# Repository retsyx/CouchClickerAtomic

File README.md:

# Couch Clicker Atomic

The keyboard for your couch.

Couch Clicker Atomic is a Bluetooth, mechanical key, home theater remote control designed for use with [Amity](https://github.com/retsyx/amity) - home theater control over HDMI-CEC that works! (really)

Watch the video

## Using Couch Clicker Atomic

Couch Clicker Atomic works with Amity like any other compatible remote. To read more about Amity and its operation, visit the [Amity page](https://github.com/retsyx/amity).

To clear Couch Clicker Atomic's Bluetooth pairing and to re-pair, press and hold the `Power` and `Volume Up` buttons for 6 seconds.

To reset Couch Clicker Atomic, press and hold the `Power` and `Mute` buttons for 6 seconds.

## It's a Keyboard

Couch Clicker Atomic is really just a standard wireless Bluetooth keyboard. It may work (with some customization) with other home theater devices that have bluetooth remote controls that are really keyboard devices, like Google TVs or Amazon Fire TVs.

## Hardware

### PCB

The remote is based on a Seeed Studio XIAO nRF52840 board. The PCB design and manufacturing files are [here](other/hardware).

### Keycaps

A sample design file to get your own keycaps from [Yuzu Keycaps](https://yuzukeycaps.com) is available [here](other/keycaps/yuzu.json).

### 3D Printed Case

STEP files for a 3D printed case are available [here](other/case).

### LiPo Battery

A LiPo with a JST 2 connector that fits in the case should work. The battery should be at most 10mm thick, and 30mm wide. Ensure the battery leads in the connector are the same polarity as the connector on Couch Clicker Atomic. If they are not, battery connector pins can be easily pried out with a utility knife to reverse their position in the connector.

[This LiPo battery](https://www.amazon.com/dp/B0CNLNZFQL) works well.

## Firmware

### ZMK

Download the ZMK firmware image from [here](https://github.com/retsyx/CouchClickerAtomic/releases/latest/download/cca-seeeduino_xiao_ble-zmk.uf2). Install it using the standard ZMK installation method - [documented here](https://zmk.dev/docs/user-setup#install-the-firmware).

When the remote is fully assembled in the case, to update the firmware, the remote must be reset to the bootloader. Press and hold the `Power`, `Select` and `Back` buttons for 10 seconds to reset to the bootloader.

Couch Clicker Atomic ZMK code is licensed under the [MIT license](MIT-LICENSE.md).

### KMK

Alternatively, you may prefer to use a CircuitPython based firmware with KMK. Code and instructions for installing KMK are [here](other/kmk).

Couch Clicker Atomic KMK code is licensed under the [GPLv3 license](GPLv3-LICENSE.md).

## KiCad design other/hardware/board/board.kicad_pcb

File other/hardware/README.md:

# Couch Clicker Atomic PCB

Gerber files and an example BOM file are in the [mfr folder](board/mfr/).

## BOM

* 1x [Seeed Studio XIAO BLE nRF52840](https://www.seeedstudio.com/Seeed-XIAO-BLE-nRF52840-p-5201.html)
* 15x [Cherry MX key switches, or similar, PCB mount](https://www.digikey.com/en/products/detail/cherry-americas-llc/MX1A-E1NW/20180)
* 15x [1N4148W diodes](https://www.digikey.com/en/products/detail/anbon-semiconductor-int-l-limited/1N4148W/17284377)
* 1x [JST 2.0 Connector](https://www.digikey.com/en/products/detail/jst-sales-america-inc/S2B-PH-K-S/926626)

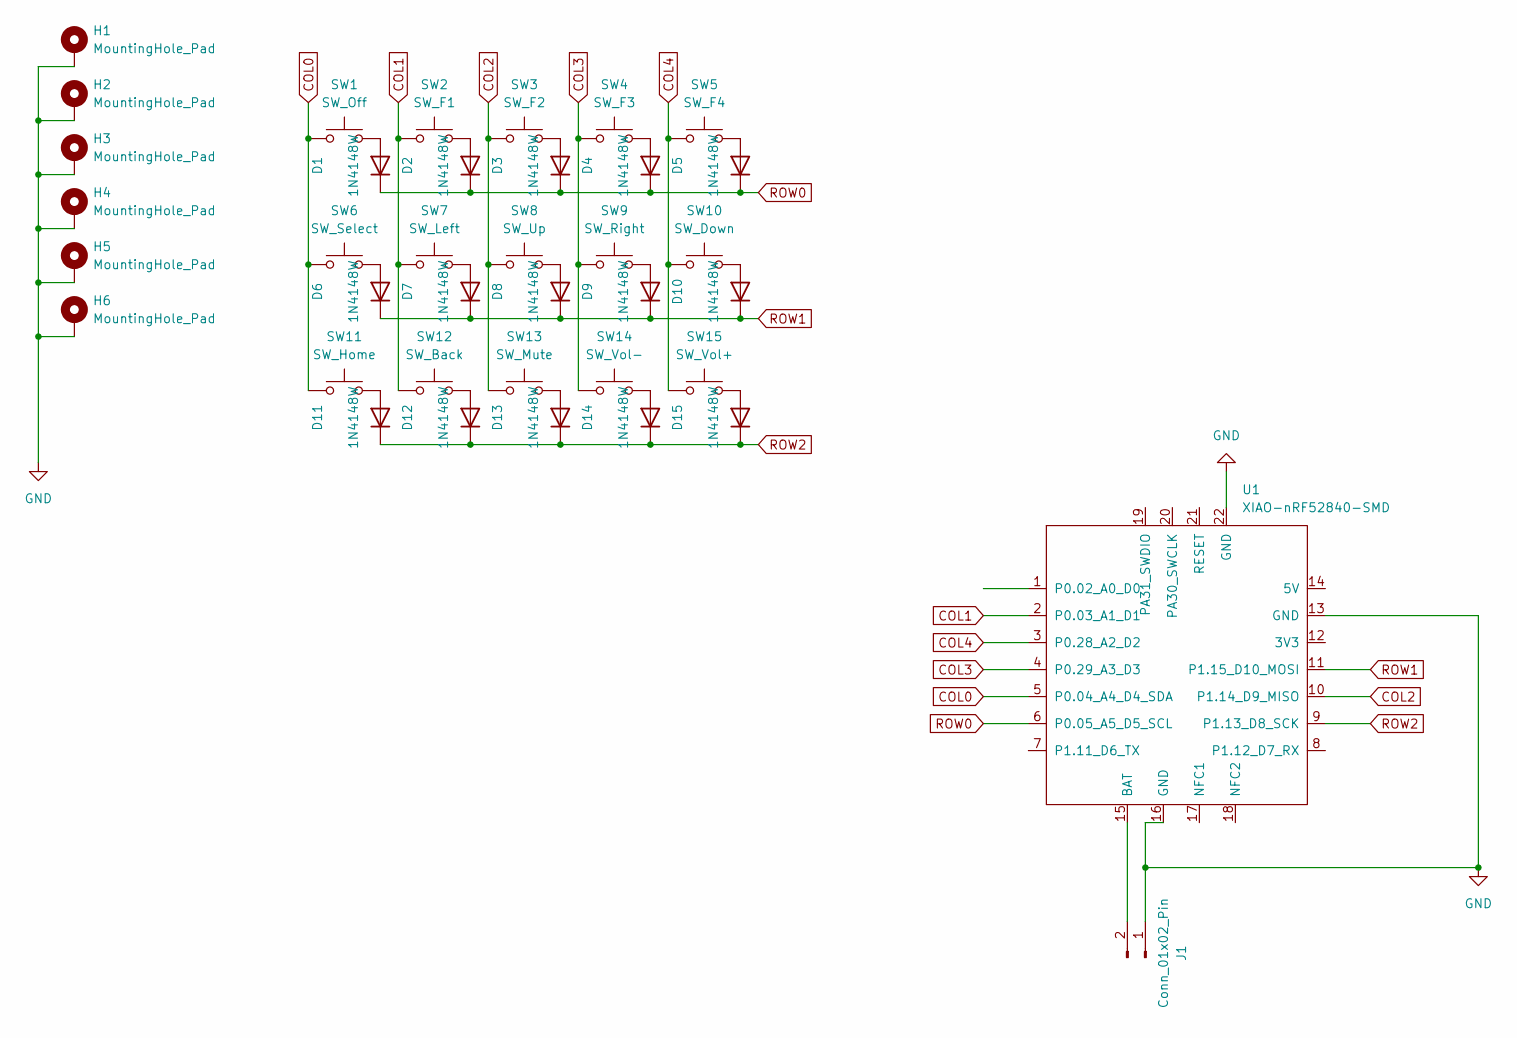
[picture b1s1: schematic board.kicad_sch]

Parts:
D1, D2, D3, D4, D5, D6, D7, D8, D9, D10, D11, D12, D13, D14, D15: 1N4148W; D_SOD-123
H1, H2, H3, H4, H5, H6: MountingHole_Pad; MountingHole_2.5mm_Pad
J1: Conn_01x02_Pin; JST_PH_S2B-PH-K_1x02_P2.00mm_Horizontal
SW1: SW_Off; SW_Cherry_MX_1.50u_PCB
SW2: SW_F1; SW_Cherry_MX_1.00u_PCB
SW3: SW_F2; SW_Cherry_MX_1.00u_PCB
SW4: SW_F3; SW_Cherry_MX_1.00u_PCB
SW5: SW_F4; SW_Cherry_MX_1.00u_PCB
SW6: SW_Select; SW_Cherry_MX_1.00u_PCB
SW7: SW_Left; SW_Cherry_MX_1.00u_PCB
SW8: SW_Up; SW_Cherry_MX_1.00u_PCB
SW9: SW_Right; SW_Cherry_MX_1.00u_PCB
SW10: SW_Down; SW_Cherry_MX_1.00u_PCB
SW11: SW_Home; SW_Cherry_MX_1.00u_PCB
SW12: SW_Back; SW_Cherry_MX_1.00u_PCB
SW13: SW_Mute; SW_Cherry_MX_1.00u_PCB
SW14: SW_Vol-; SW_Cherry_MX_1.00u_PCB
SW15: SW_Vol+; SW_Cherry_MX_1.00u_PCB
U1: XIAO-nRF52840-SMD

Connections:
COL0: SW1.1, SW6.1, SW11.1, U1.5 (P0.04_A4_D4_SDA)
COL1: SW2.1, SW7.1, SW12.1, U1.2 (P0.03_A1_D1)
COL2: SW3.1, SW8.1, SW13.1, U1.10 (P1.14_D9_MISO)
COL3: SW4.1, SW9.1, SW14.1, U1.4 (P0.29_A3_D3)
COL4: SW5.1, SW10.1, SW15.1, U1.3 (P0.28_A2_D2)
GND: H1.1, H2.1, H3.1, H4.1, H5.1, H6.1, J1.1, U1.13 (GND), U1.16 (GND), U1.22 (GND)
unnamed: D1.2 (A), SW1.2
unnamed: D2.2 (A), SW2.2
unnamed: D3.2 (A), SW3.2
unnamed: D4.2 (A), SW4.2
unnamed: D5.2 (A), SW5.2
unnamed: D6.2 (A), SW6.2
unnamed: D7.2 (A), SW7.2
unnamed: D8.2 (A), SW8.2
unnamed: D9.2 (A), SW9.2
unnamed: D10.2 (A), SW10.2
unnamed: D11.2 (A), SW11.2
unnamed: D12.2 (A), SW12.2
unnamed: D13.2 (A), SW13.2
unnamed: D14.2 (A), SW14.2
unnamed: D15.2 (A), SW15.2
unnamed: J1.2, U1.15 (BAT)
ROW0: D1.1 (K), D2.1 (K), D3.1 (K), D4.1 (K), D5.1 (K), U1.6 (P0.05_A5_D5_SCL)
ROW1: D6.1 (K), D7.1 (K), D8.1 (K), D9.1 (K), D10.1 (K), U1.11 (P1.15_D10_MOSI)
ROW2: D11.1 (K), D12.1 (K), D13.1 (K), D14.1 (K), D15.1 (K), U1.9 (P1.13_D8_SCK)

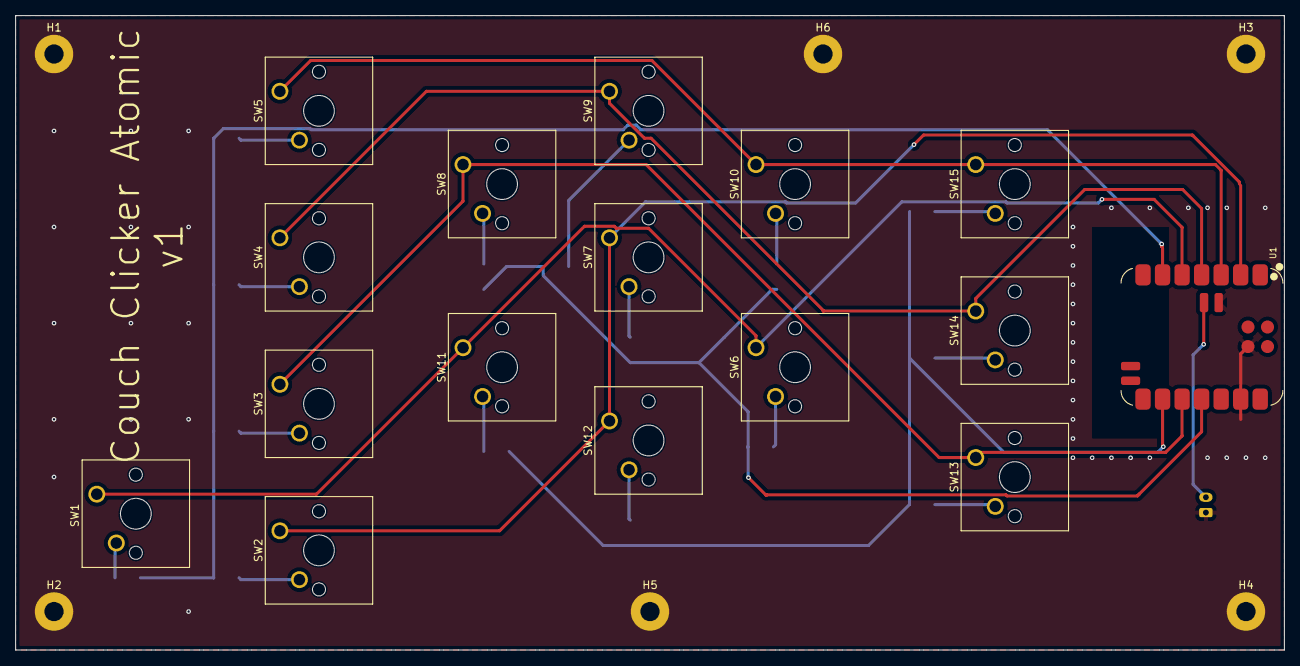
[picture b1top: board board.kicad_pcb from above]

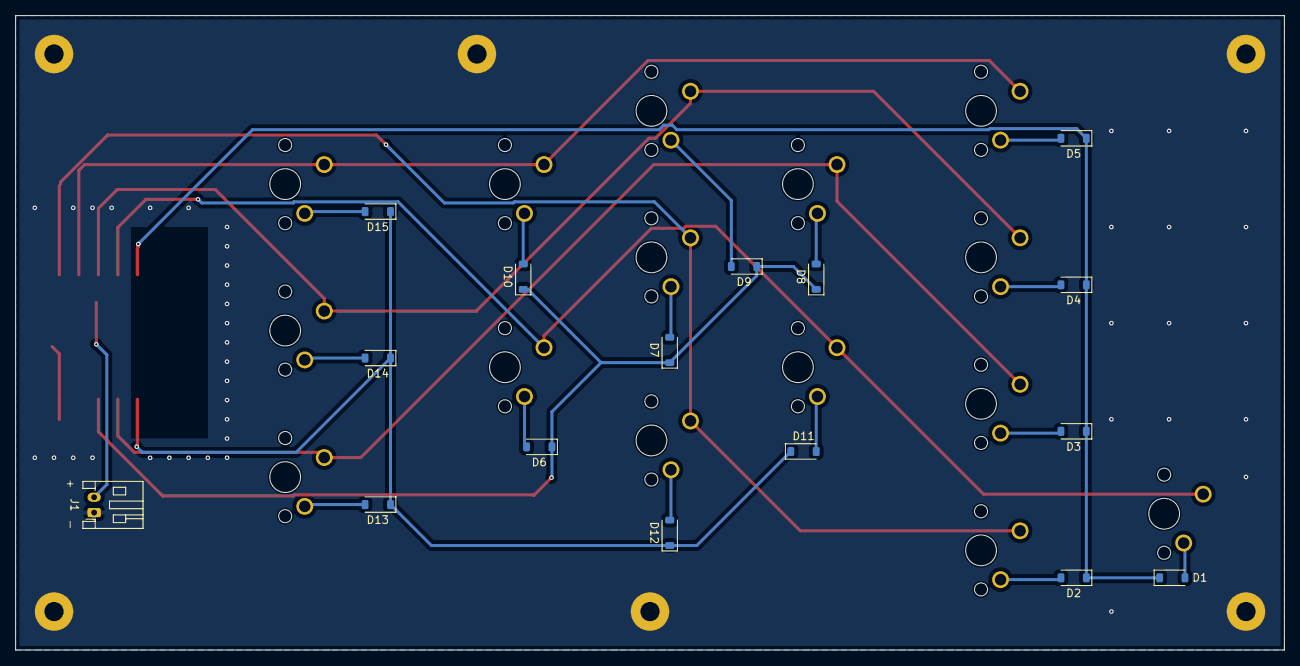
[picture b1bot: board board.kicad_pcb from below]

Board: 2 copper layers, 165.0 x 82.5 mm, 38 parts (16 on the bottom side), 25 nets.

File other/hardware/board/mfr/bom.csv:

Item #,Designator,Qty,Manufacturer,Mfg Part #,Descrption / Value,Package / Footprint,Type
1,"SW1,SW2,SW3,SW4,SW5,SW6,SW7,SW8,SW9,SW10,SW11,SW12,SW13,SW14,SW15",15,Cherry Americas LLC,CH197-ND,SWITCH PUSH SPST-NO 0.01A 12V,Through Hole,Through Hole
2,"D1,D2,D3,D4,D5,D6,D7,D8,D9,D10,D11,D12,D13,D14,D15",15,"ANBON SEMICONDUCTOR (INT'L) LIMITED",1N4148W,DIODE STANDARD 75V 150MA SOD123,SOD123,SMD
3,U1,1,Seeed Studio,102010448,XIAO nRF52840,SMD,SMD
4,J1,1,JST,S2B-PH-K-S,CONN HEADER R/A 2POS 2MM,Through Hole,Through Hole

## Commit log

2026-01-18 Add .gitignore
2026-01-24 Yuzu keycap definition file
2026-01-25 Initial functionality
2026-01-26 BT unpair and reset on long hold of combos
    Press and hold power + mute for 6 seconds to reset/restart the firmware
    Press and hold power + volume up for 6 seconds to unbind/unpair bluetooth
2026-01-26 Increase BLE TX power
2026-01-29 Add reset to bootloader key combo
    10 second hold of power, back/esc, and select resets to the bootloader.
2026-01-30 Disable USB
2026-02-03 Add HW design, KMK firmware, and documentation
